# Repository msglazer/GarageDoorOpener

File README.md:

# GarageDoorOpener
Garage door opener keyfob replacement that can detect door position and allows for OK google commands. As well as a distance sensor and LEDs to show distance from garage wall.

## Hardware:
### Power Board

Features:
* 120V AC/DC converter to 24V, 20W output
* Two reed switch connectors 
* One relay control connector
* RJ45 connector for cable to control board

### Control Board

Features:
* Particle Boron Microcontroller with cellular connectivity
* 24V to 5W switching regulator
* ToF sensor for range finding
* LED header for visualizing distance
* RJ45 connector for power/control

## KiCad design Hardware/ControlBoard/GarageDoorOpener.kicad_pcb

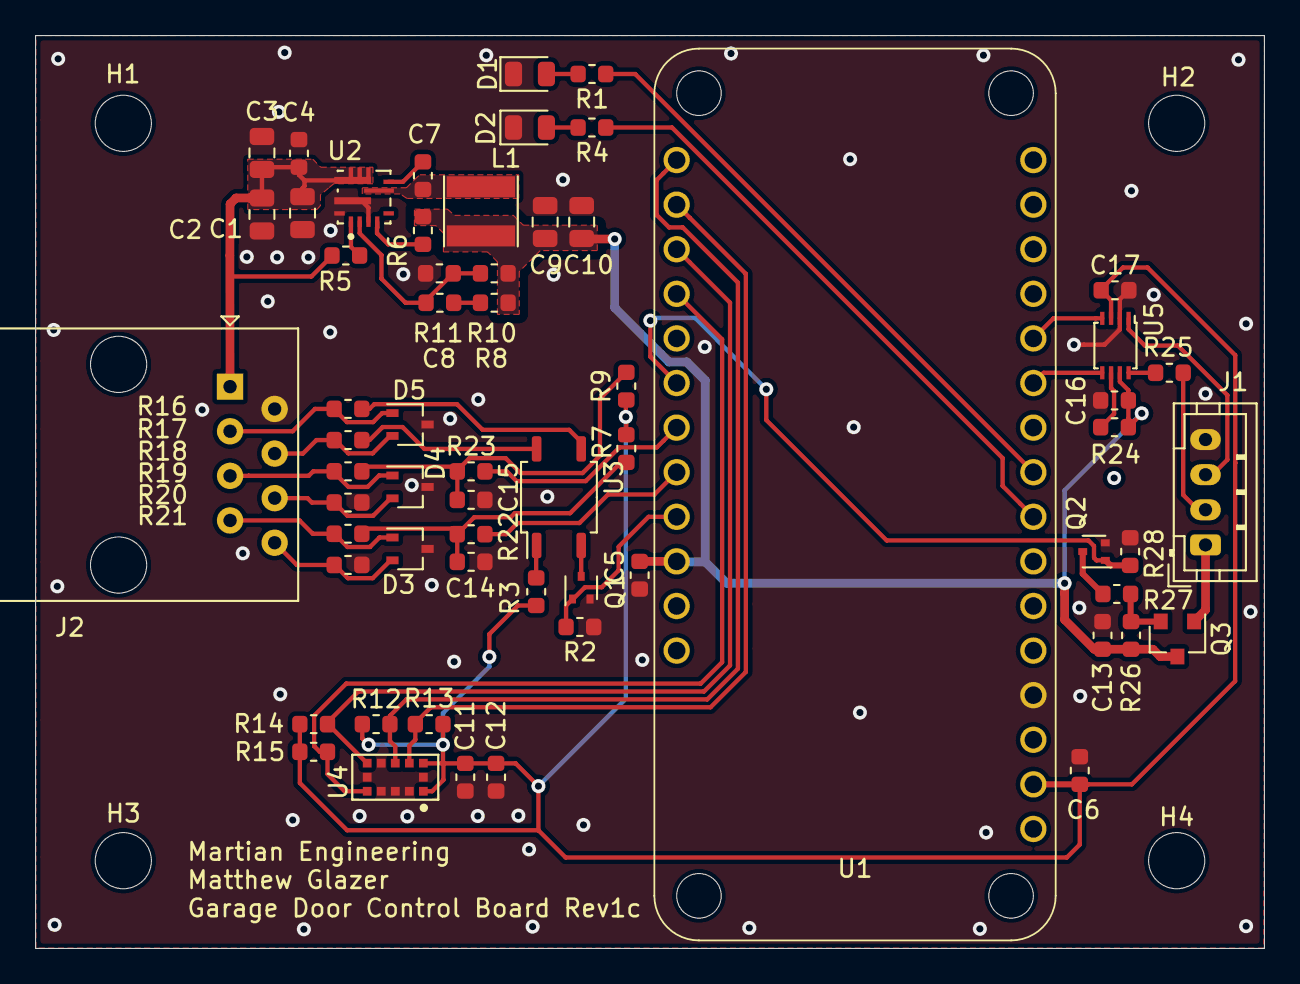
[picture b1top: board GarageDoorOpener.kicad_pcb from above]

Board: 2 copper layers, 70.0 x 52.0 mm, 65 parts (0 on the bottom side), 43 nets.

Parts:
C1, C2, C3: 4.7uF 50V; C_0805_2012Metric
C4: 0.1uF 50V; C_0603_1608Metric
C5, C6, C16, C17: 1uF 10V; C_0603_1608Metric
C7, C12: 0.1uF 16V; C_0603_1608Metric
C8: 100pF 10V; C_0603_1608Metric
C9, C10: 22uF 10V; C_0805_2012Metric
C11, C13: 4.7uF 10V; C_0603_1608Metric
C14, C15: 2.2uF 10V; C_0603_1608Metric
D1: GREEN_LED; LED_0805_2012Metric
D2: RED_LED; LED_0805_2012Metric
D3, D4, D5: DF3A5.6LFU,LF; SOT-323_SC-70
H1, H2, H3, H4: MountingHole; MountingHole_3.2mm_M3
J1: Conn_01x04; JST_PH_B4B-PH-K_1x04_P2.00mm_Vertical
J2: RJ45; RJ45_Amphenol_54602-x08_Horizontal
L1: 3.3uH; L_Taiyo-Yuden_NR-40xx
Q1, Q2: DMG1012T-7; SOT-523
Q3: SSM6J422TU,LF; SOT-23
R1, R3, R4: 649; R_0603_1608Metric
R2, R5, R6, R7, R9, R11, R14, R15, R24, R26, R28: 10K; R_0603_1608Metric
R8: 20K; R_0603_1608Metric
R10: 73.2K; R_0603_1608Metric
R12, R13: 4.7K; R_0603_1608Metric
R16, R17, R18, R19, R20, R21: 0; R_0603_1608Metric
R22, R23, R25: 226; R_0603_1608Metric
R27: 49.9; R_0603_1608Metric
U1: Argon/Boron; ParticleBoron
U2: TPS56637; TPS56637RPAR
U3: CPC1002N; SOP-4_3.8x4.1mm_P2.54mm
U4: VL53L1X; VL53L1CXV0FY_1
U5: TXB0102DCU; VSSOP-8_2.4x2.1mm_P0.5mm

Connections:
+3V3: C6.1, C11.1, C12.1, C17.1, R3.2, R7.1, R9.1, R12.1, R13.1, R14.1, R15.1, U1.2, U4.1, U4.11, U5.3
+5V: C5.1, C9.2, C10.2, C13.1, C16.1, L1.2, Q3.3, R6.1, R8.2, R10.2, R24.2, R26.1, U1.26, U5.7
+24V: C1.1, C2.1, C3.1, C4.1, J2.1, R5.1, U2.8
/CONNECTIVITY_LED: R1.1, U1.9
/LED_PWR_TOGGLE: Q2.1, R28.2, U1.22
/LED_STRIP_CLK: U1.11, U5.5
/LED_STRIP_DATA: U1.12, U5.4
/REED_SW1_IN: R22.2, U1.24
/REED_SW1_RJ45: C14.1, R7.2, R20.2, R22.1
/REED_SW2_IN: R23.2, U1.23
/REED_SW2_RJ45: C15.1, R9.2, R18.2, R23.1
/RELAY_CTRL1: Q1.1, R2.2, U1.25
/Relay_Ouput1: R16.2, U3.3
/Relay_Ouput2: R17.2, U3.4
/SENSOR_I2C_SCL: R13.2, U1.18, U4.10
/SENSOR_I2C_SDA: R12.2, U1.17, U4.9
/SENSOR_INT: R14.2, U1.19, U4.7
/STATUS_LED: R4.1, U1.8
/~SENSOR_SHUTDOWN: R15.2, U1.20, U4.5
GND: C1.2, C2.2, C3.2, C4.2, C5.2, C6.2, C9.1, C10.1, C11.2, C12.2, C13.2, C14.2, C15.2, C16.2, C17.2, D1.1, D2.1, D3.3, D4.3, D5.3, J1.4, J2.2, Q1.2, Q2.2, R2.1, R11.1, R19.2, R21.2, R28.1, U1.4, U2.3, U2.9, U2.10, U4.2, U4.3, U4.4, U4.6, U4.8, U4.12, U5.2
unnamed: C7.1, L1.1, U2.6
unnamed: C7.2, U2.7
unnamed: C8.1, R10.1, R11.2, U2.2
unnamed: C8.2, R8.1
unnamed: D1.2, R1.2
unnamed: D2.2, R4.2
unnamed: D3.1, J2.7, R20.1
unnamed: D3.2, J2.8, R21.1
unnamed: D4.1, J2.5, R18.1
unnamed: D4.2, J2.6, R19.1
unnamed: D5.1, J2.3, R16.1
unnamed: D5.2, J2.4, R17.1
unnamed: J1.1, Q3.1
unnamed: J1.2, R25.1
unnamed: J1.3, U5.1
unnamed: Q1.3, U3.2
unnamed: Q2.3, R27.1
unnamed: Q3.2, R26.2, R27.2
unnamed: R3.1, U3.1
unnamed: R5.2, U2.1
unnamed: R6.2, U2.4
unnamed: R24.1, U5.6
unnamed: R25.2, U5.8

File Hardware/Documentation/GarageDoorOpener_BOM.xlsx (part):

Board | Number | Unit Qty | RefDes | Value | Manufacturer | Dist. Part # | Mfg Part # | Price Each | Total Price | Description | Package | Type | Datasheet
Control | 1 | 1 | U1 | 4G MCU | Particle | 1878-1023-ND | BRN402 | 49.28 | 49.28 | BORON LTE Microcontroller | Feather | Thru-hole | https://media.digikey.com/pdf/Data%20Sheets/Particle%20PDFs/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
Control | 2 | 1 | U2 | Switching Regulator | Texas Instruments | 296-TPS56637RPARCT-ND | TPS56637RPAR | 3.5 | 3.5 | Buck Switching Regulator IC Positive Adjustable 0.6V 1 Output 6A 10-PowerVFQFN | 10-PowerVFQFN | SMD | http://www.ti.com/general/docs/suppproductinfo.tsp?distId=10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
Control | 3 | 1 | U3 | Solid State Relay | IXYS Integrated Circuits Division | CLA221-ND | CPC1002N | 1.08 | 1.08 | Solid State SPST-NO (1 Form A) 4-SOP (0.150", 3.81mm) | 4-SOP (0.150", 3.81mm) | SMD | http://www.ixysic.com/home/pdfs.nsf/www/CPC1002N.pdf/$file/C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
Control | 4 | 1 | U4 | ToF Sensor | STMicroelectronics | 497-17764-1-ND | VL53L1CXV0FY/1 | 6.43 | 6.43 | Optical Sensor 157.480" (4m) I²C Output | LGA-12 | SMD | https://www.mouser.com/datasheet/2/389/dm00452094-1799360.pdf
Control | 5 | 1 | U5 | Level Shifter | Texas Instruments | 296-22862-6-ND | TXB0102DCUR | 0.71 | 0.71 | Voltage Level Translator Bidirectional 1 Circuit 2 Channel 100Mbps 8-VSSOP | 8-VSSOP | SMD | http://www.ti.com/general/docs/suppproductinfo.tsp?distId=10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
Control | 6 | 2 | Q1,Q2 | NMOS FET | Diodes Inc | DMG1012T-7DICT-ND | DMG1012T-7 | 0.28999999999999998 | 0.57999999999999996 | N-Channel 20V 630mA (Ta) 280mW (Ta) Surface Mount SOT-523 | SOT-523 | SMD | https://www.diodes.com/assets/Datasheets/ds31783.pdf
Control | 7 | 1 | Q3 | PMOS FET | Nexperia USA Inc. | 1727-2310-1-ND | PMV65XPEAR | 0.36 | 0.36 | P-Channel 20V 2.8A (Ta) 480mW (Ta), 6.25W (Tc) Surface Mount TO-236AB | SOT-23-3 | SMD | https://assets.nexperia.com/documents/data-sheet/PMV65XPEA.pdf
Control | 8 | 1 | L1 | Switching regulator inductor | Taiyo Yuden | 587-2892-1-ND | NRS4018T3R3MDGJ | 0.28999999999999998 | 0.28999999999999998 | 3.3µH Shielded Wirewound Inductor 2A 66mOhm Max Nonstandard | 4mm x 4mm | SMD | https://www.yuden.co.jp/productdata/catalog/wound04_e.pdf
Control | 9 | 1 | D1 | Green LED | Würth Elektronik | 732-4986-1-ND | 150080VS75000 | 0.18 | 0.18 | Green 570nm LED Indication - Discrete 2V 0805 (2012 Metric) | 0805 | SMD | https://katalog.we-online.de/led/datasheet/150080VS75000.pdf
Control | 10 | 1 | D2 | Red LED | Würth Elektronik | 732-4985-1-ND | 150080SS75000 | 0.18 | 0.18 | Red 630nm LED Indication - Discrete 1.9V 0805 (2012 Metric) | 0805 | SMD | https://katalog.we-online.de/led/datasheet/150080SS75000.pdf
Control | 11 | 3 | D3,D4,D5 | TVS diode array (2 channel) | Toshiba Semiconductor and Storage | DF3A5.6LFULFCT-ND | DF3A5.6LFU,LF | 0.28999999999999998 | 0.86999999999999988 | 3V (Typ) Clamp 5A (8/20µs) Ipp Tvs Diode Surface Mount 7-XSON (1.1x2.1) | 7-XSON | SMD | https://assets.nexperia.com/documents/data-sheet/PUSB3FR6.pdf
Control | 12 | 3 | C1,C2,C3 | 4.7uF 50V | Murata Electronics | 490-10751-1-ND | GRM21BR61H475KE51L | 0.41 | 1.23 | 4.7µF ±10% 50V Ceramic Capacitor X5R 0805 (2012 Metric) | 0805 | SMD | https://search.murata.co.jp/Ceramy/image/img/A01X/G101/ENG/G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
Control | 13 | 1 | C4 | 0.1uF 50V | KEMET | 399-7845-1-ND | C0603C104M5RACTU | 0.1 | 0.1 | 0.1µF ±20% 50V Ceramic Capacitor X7R 0603 (1608 Metric) | 0603 | SMD | https://api.kemet.com/component-edge/download/datasheet/C060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
Control | 14 | 4 | C5,C6,C16,C17 | 1uF 10V | Samsung Electro-Mechanics | 1276-1182-1-ND | CL10A105KP8NNNC | 0.1 | 0.4 | 1µF ±10% 10V Ceramic Capacitor X5R 0603 (1608 Metric) | 0603 | SMD | https://media.digikey.com/pdf/Data%20Sheets/Samsung%20PDFs/C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
Control | 15 | 2 | C7,C12 | 0.1uF 16V | KEMET | 399-1099-1-ND | C0603C104M4RACTU | 0.1 | 0.2 | 0.1µF ±20% 16V Ceramic Capacitor X7R 0603 (1608 Metric) | 0603 | SMD | https://api.kemet.com/component-edge/download/datasheet/C060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
Control | 16 | 1 | C8 | 100pF 10V | Würth Elektronik | 732-7922-1-ND | 885012206003 | 0.1 | 0.1 | 100pF ±10% 10V Ceramic Capacitor X7R 0603 (1608 Metric) | 0603 | SMD | https://katalog.we-online.de/pbs/datasheet/885012206003.pdf
Control | 17 | 2 | C9,C10 | 22uF 10V | Taiyo Yuden | 587-5464-1-ND | LMK212BBJ226MG-T | 0.3 | 0.6 | 22µF ±20% 10V Ceramic Capacitor X5R 0805 (2012 Metric) | 0805 | SMD | https://ds.yuden.co.jp/TYCOMPAS/ut/detail?pn=LMK212BBJ226MG-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
Control | 18 | 2 | C11,C13 | 4.7uF 10V | Taiyo Yuden | 587-1441-1-ND | LMK107BJ475KA-T | 0.19 | 0.38 | 4.7µF ±10% 10V Ceramic Capacitor X5R 0603 (1608 Metric) | 0603 | SMD | https://ds.yuden.co.jp/TYCOMPAS/ut/detail?pn=LMK107BJ475KA-T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
Control | 19 | 2 | C14,C15 | 2.2uF Cap
Control | 20 | 3 | R1,R3,R4 | 649 ohm 1% | Stackpole Electronics | RMCF0603FT649RCT-ND | RMCF0603FT649R | 0.1 | 0.30000000000000004 | 649 Ohms ±1% 0.1W, 1/10W Chip Resistor 0603 (1608 Metric) Automotive AEC-Q200 T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 | 0603 | SMD | https://www.seielect.com/catalog/sei-rmcf_rmcp.pdf
Control | 21 | 11 | R2,R5,R6,R7,R9,R14,R15,R24,R26,R28 | 10K ohm 5% | Stackpole Electronics | RMCF0603JT10K0CT-ND | RMCF0603JT10K0 | 0.1 | 1.1000000000000001 | 10 kOhms ±5% 0.1W, 1/10W Chip Resistor 0603 (1608 Metric) Automotive AEC-Q200 T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 | 0603 | SMD | https://www.seielect.com/catalog/sei-packaging.pdf
Control | 22 | 1 | R11 | 10K ohm 1% | Yageo | 311-10.0KHRCT-ND | RC0603FR-0710KL | 0.1 | 0.1 | 10 kOhms ±1% 0.1W, 1/10W Chip Resistor 0603 (1608 Metric) Moisture Resistant Th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 | 0603 | SMD | https://www.yageo.com/upload/media/product/productsearch/dat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
Control | 23 | 1 | R8 | 20K ohm 1% | Yageo | 311-20.0KHRCT-ND | RC0603FR-0720KL | 1 | 1 | RES SMD 20K OHM 1% 1/10W 0603 | 0603 | SMD | https://www.yageo.com/upload/media/product/productsearch/dat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
Control | 24 | 1 | R10 | 73.2K ohm 1% | KOA Speer Electronics, Inc. | 2019-RK73H1JTTD7322FCT-ND | RK73H1JTTD7322F | 0.1 | 0.1 | 73.2 kOhms ±1% 0.1W, 1/10W Chip Resistor 0603 (1608 Metric) Automotive AEC-Q200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 | 0603 | SMD | http://www.koaspeer.com/pdfs/RK73H.pdf
Control | 25 | 2 | R12,R13 | 4.7K ohm 5% | Yageo | 311-4.7KGRCT-ND | RC0603JR-074K7L | 0.1 | 0.2 | 4.7 kOhms ±5% 0.1W, 1/10W Chip Resistor 0603 (1608 Metric) Moisture Resistant T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 | 0603 | SMD | https://www.yageo.com/upload/media/product/productsearch/dat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
Control | 26 | 6 | R16,R17,R18,R19,R20,R21 | 0 ohm | Yageo | 311-0.0GRCT-ND | RC0603JR-070RL | 0.1 | 0.60000000000000009 | 0 Ohms Jumper 0.1W, 1/10W Chip Resistor 0603 (1608 Metric) Moisture Resistant T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 | 0603 | SMD | https://www.yageo.com/upload/media/product/productsearch/dat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
Control | 27 | 3 | R22.R23,R25 | 226 ohm
Control | 28 | 1 | J1 |  | LED header |  |  |  | 0
Control | 29 | 1 | J2 | RJ45 Connector | Amphenol ICC (FCI) | 609-1046-ND | 54602-908LF | 0.62 | 0.62 | Jack Modular Connector 8p8c (RJ45, Ethernet) 90° Angle (Right) Unshielded Cat3 | RJ45 | Thru-hole | https://cdn.amphenol-icc.com/media/wysiwyg/files/documentati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
Control | 30 | 1 | PWR_IN1 | power inlet | Qualtek | Q840-ND | 770W-X2/13 | 0.77 | 0.77 | Power Entry Connector Receptacle, Male Pins IEC 320-C8 Panel Mount, Snap-In | 24.5x12.5 | Panel Mount | http://www.qualtekusa.com/images/AC_Receptacles/pdfs/770wx213.pdf
Control | 31 | 1 | CABLE1 | 120V cord | Qualtek | Q536-ND | 223082-01 | 3.95 | 3.95 | 6.00' (1.83m) Power Cord Black NEMA 1-15P, Polarized To IEC 320-C7, Polarized S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 | Cable | Thru-hole | http://www.qualtekusa.com/images/Power%20Cords/PDF%20Files/2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
Control | 32 | 1 | ANT1 | 4G antenna | Taoglas Limited | 931-1329-ND | FXUB63.07.0150C | 9.82 | 9.82 | 850MHz, 1.575GHz, 1.8GHz, 2.1GHz, 2.4GHz, 2.6GHz GPS, LTE, Wi-Fi Flat Patch RF 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 | flex PCB | UFL | https://cdn.taoglas.com/datasheets/FXUB63.07.0150C.pdf
Control | 33 | 1 | PCB1 |  | OshPark |  |  | 11.253753333333334 | 11.253753333333334 |  | Rigid PCB
Control | 34 | 1 | LEDSTRIP1 |  | SparkFun | COM-14015 |  | 8.0288000000000004 | 8.0288000000000004 | LED RGB Strip - Addressable, 1m (APA102)
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
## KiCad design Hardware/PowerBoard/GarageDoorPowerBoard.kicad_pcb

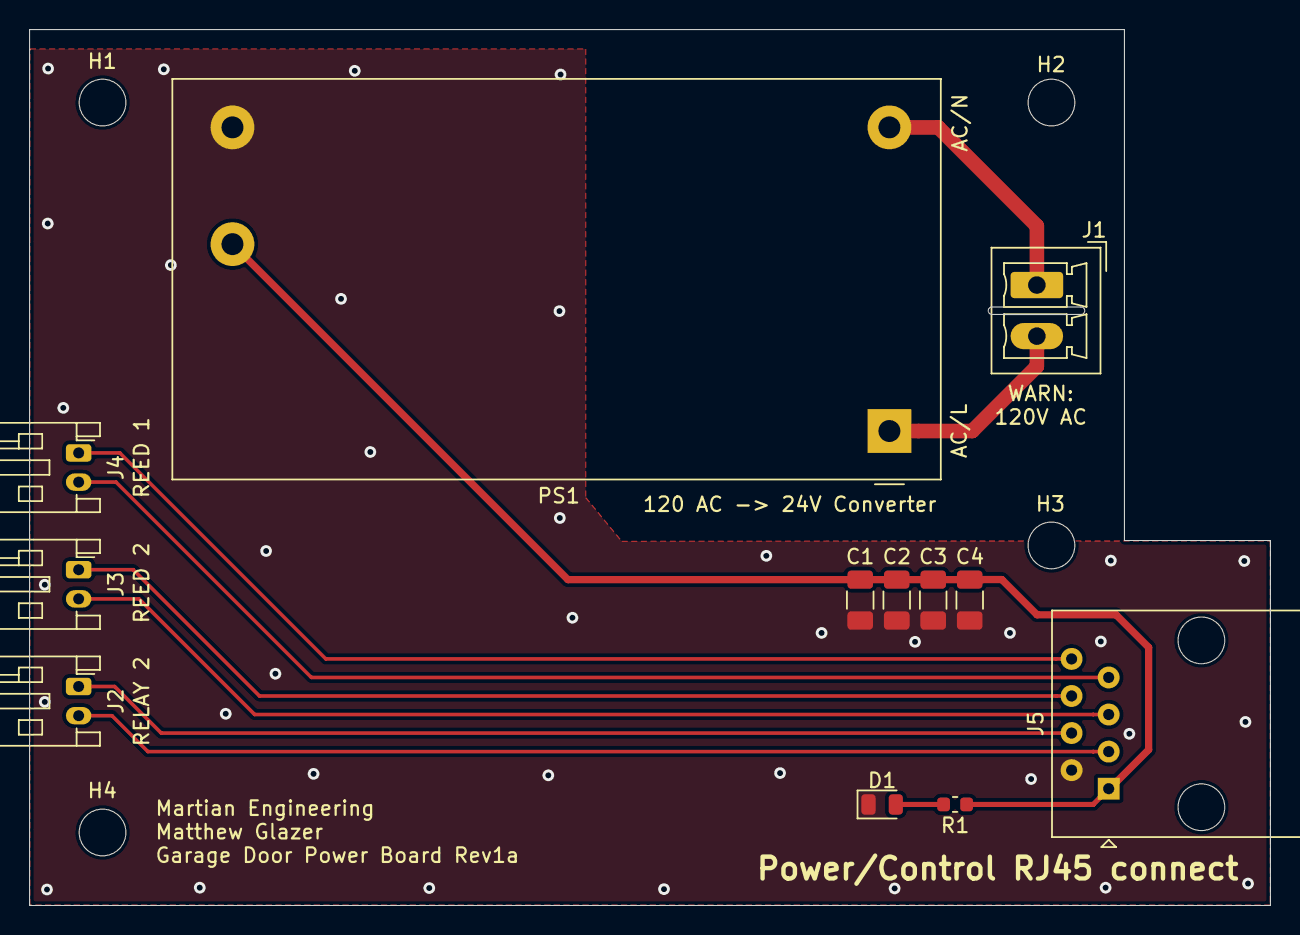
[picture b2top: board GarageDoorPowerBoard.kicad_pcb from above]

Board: 2 copper layers, 85.0 x 60.0 mm, 16 parts (0 on the bottom side), 11 nets.

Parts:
C1, C2, C3, C4: 22uF 35V; C_1206_3216Metric
D1: GREEN LED; LED_0805_2012Metric
H1, H2, H3, H4: MountingHole; MountingHole_3.2mm_M3
J1: 1984617; PhoenixContact_MCV_1,5_2-G-3.5_1x02_P3.50mm_Vertical
J2, J3, J4: JST-PH2; JST_PH_S2B-PH-K_1x02_P2.00mm_Horizontal
J5: RJ45; RJ45_Amphenol_54602-x08_Horizontal
PS1: IRM-20-24; Converter_ACDC_MeanWell_IRM-20-xx_THT
R1: 4.7K; R_0603_1608Metric

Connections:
+24V: C1.1, C2.1, C3.1, C4.1, J5.1, PS1.4, R1.1
/REED_SW1_GND: J4.1, J5.8
/REED_SW1_IN: J4.2, J5.7
/REED_SW2_GND: J3.1, J5.6
/REED_SW2_IN: J3.2, J5.5
/Relay_Output1: J2.2, J5.3
/Relay_Output2: J2.1, J5.4
GND: C1.2, C2.2, C3.2, C4.2, D1.1, J5.2, PS1.3
unnamed: D1.2, R1.2
unnamed: J1.1, PS1.2
unnamed: J1.2, PS1.1

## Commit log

2020-04-28 Intital schematic started as well as some supporting documentation
2020-04-29 small amount of work done, added some documentation
2020-05-01 first pass on the schematic done
2020-05-01 Re-arranged the files in the repo
2020-05-01 schematic slightly updated (footprint association) PCB started
2020-05-03 scope creep is great, decided to expand on the project a bit, Rev1b
2020-05-03 I moved files again, added the power board schematic, working on BoM
2020-05-05 Schematics done, PCBs have components dropped in and BoM finished
2020-05-07 started work on the power PCB, board shape and basic placement complete
2020-05-08 PCB finished for power board
2020-05-08 Power Board Gerbers!
2020-05-09 working on the PCB for the control board
2020-05-10 placement of components 80% board outline done
2020-05-10 first pass of completed control board done
2020-05-11 minor tweaks as I was making a readme
2020-05-11 CAD models and updated PCBs per readme changes (pictures)
2020-05-19 Power Board gerbers
2020-05-19 minor tweaks, powerboard ready!
2020-05-19 added some bits to the schematic, BoM updated
2020-05-20 Control Board Gerbers generated
2020-05-20 finished the control board, ordered PCBs!
2020-06-13 added some step files
2020-06-28 turns out setting up a project and starting the code adds a lot of files
